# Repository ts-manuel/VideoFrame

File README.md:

# Video Frame

<!-- TABLE OF CONTENTS -->
<details open="open">
  <summary>Table of Contents</summary>
  <ol>
    <li>
      <a href="#about-the-project">About The Project</a>
    </li>
    <li>
      <a href="#getting-started">Getting Started</a>
      <ul>
        <li><a href="#prerequisites">Prerequisites</a></li>
        <li><a href="#compiling">Compiling</a></li>
        <li><a href="#usb-bootloader">USB Bootloader</a></li>
      </ul>
    </li>
    <li><a href="#how-to-operate">How to Operate</a></li>
      <ul>
        <li><a href="#circuit-diagram">Circuit Diagram</a></li>
        <li><a href="#buttons">Buttons</a></li>
        <li><a href="#configuration-through-usb">Configuration through USB</a></li>
      </ul>
    <li><a href="#disclaimer">Disclaimer</a></li>
  </ol>
</details>

<!-- ABOUT THE PROJECT -->
## About The Project
This is a digital picture frame that plays movies at one frame per minute. Images appear on a [7-Color ePaper display](https://www.waveshare.com/5.65inch-e-paper-module-f.htm). The whole movie is stored as a sequence of jpeg images on an SD-Card. An STM32 microcontroller does the jpeg decoding and drives the display.

e-Paper displays maintain the displayed image without needing any power. The image is updated every 24 minutes and an update cycle takes 18 seconds. Since the device is in sleep mode for the majority of the time, power draw is minimal and the batteries last for a decent amount of time.

The device is powered by 6 AA batteries.

For more info check out the [full log on hackaday.io](https://hackaday.io/project/177197-the-slowest-video-player-with-7-colors)

<!-- GETTING STARTED -->
## Getting Started
### Prerequisites
* [STM32CubeIDE 1.4.0](https://www.st.com/en/development-tools/stm32cubeide.html)
* [dfu-util](http://dfu-util.sourceforge.net/)

### Compiling
* Open STM32CubeIDE
* Select a folder as workspace (this can be any folder in your hard-drive)
* Click on `File > Import`
* Select `General > Existing Project into Workspace` then click next
* Browse for the folder `stm32` select the project and click finish

### USB bootloader
* Connect the USB cable, check that the [correct drivers](https://www.hanselman.com/blog/how-to-fix-dfuutil-stm-winusb-zadig-bootloaders-and-other-firmware-flashing-issues-on-windows) are installed
* Enter DFU mode by pressing the RESET while holding down the BOOT button
* Use the following command to flash the firmware

      dfu-util -a0 -s 0x08000000 0 -D "Video Frame.bin"

<!-- HOW TO OPERATE -->
## How to Operate
### Circuit Diagram

### Buttons
* **RESET**: Press during sleep to wake the microcontroller and initiate a display update cycle.
* **BOOT**: Hold down during reset to enter DFU mode. Press during display update to receive commands from the serial port.

### Configuration through USB
The USB emulates a serial port that can be used to configure the device. During normal operation, a timer interrupt wakes the microcontroller every 24 minutes to update the display. An update cycle can also be triggered by pressing the **RESET** button. By default, the microcontroller goes back into sleep mode immediately after the display has been updated. By pressing the **BOOT** button while the display is updating, the microcontroller starts listening for commands on the serial port. After 60 seconds of inactivity, the microcontroller goes back to sleep.

The following is a list of commands that can be entered.
> ***load FOLDER/FILE.jpg*** loads the specified file from the SD card

> ***update*** triggers an update cycle

> ***sleep*** enters sleep mode immediately

<!-- DISCLAIMER -->
## Disclaimer
The following project is shared "as is", with the sole objective of being useful. The creator of the described piece of hardware and its associated software cannot guarantee its correct functioning under any circumstance. The author of this project will not be held responsible for any material, personal or economic losses to you or any third parties that may arise from using this design. This project will not be used under any circumstances on systems whose responsibility is critical, or from which people's lives depend upon, directly or indirectly.

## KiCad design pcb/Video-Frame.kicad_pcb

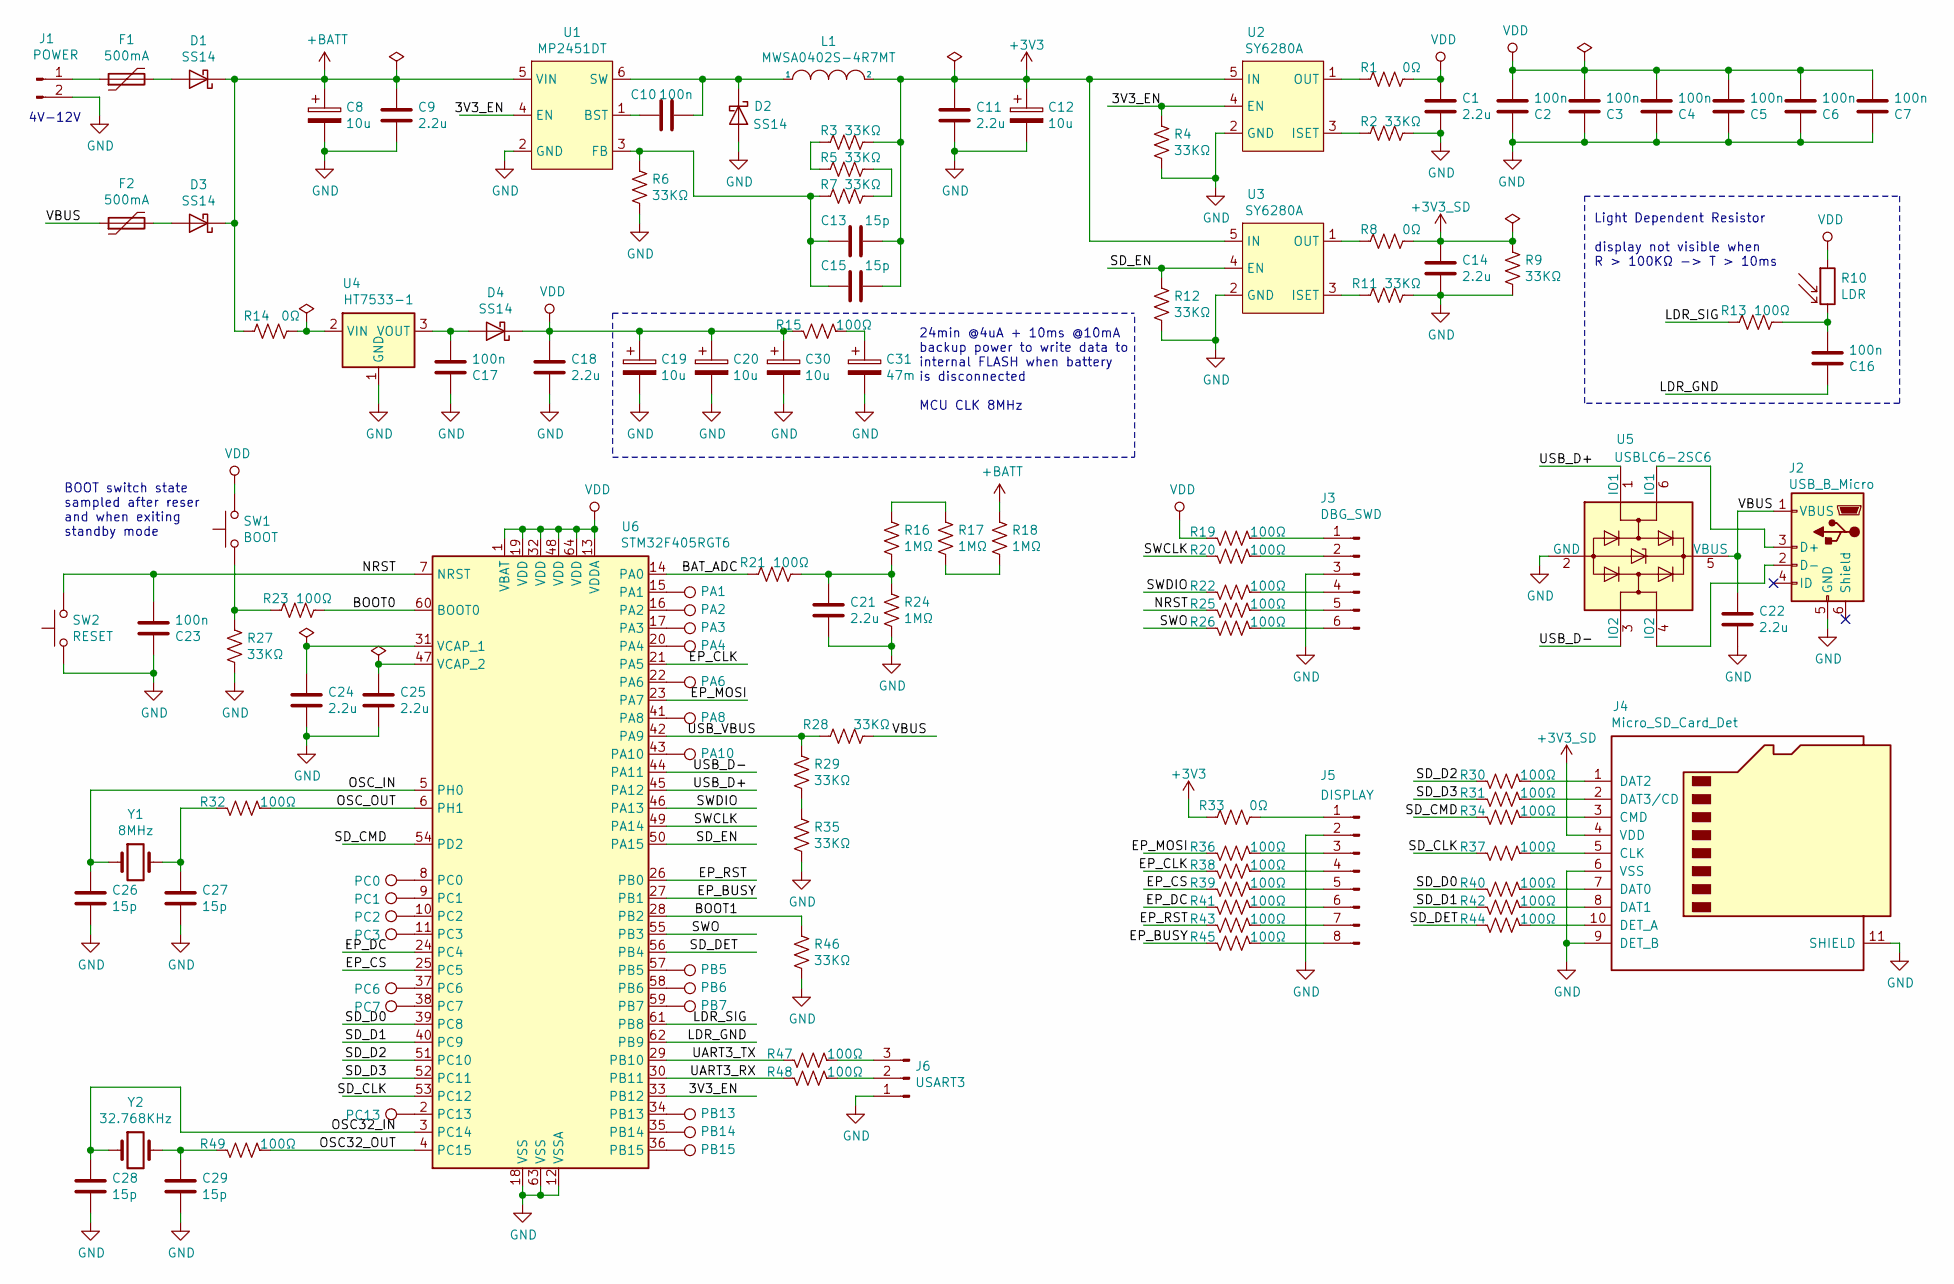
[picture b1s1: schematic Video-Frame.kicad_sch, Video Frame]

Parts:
C1, C9, C11, C14, C18, C21, C22, C24, C25: 2.2u; C_0603_1608Metric; LCSC Footprint 0603
C2, C3, C4, C5, C6, C7, C10, C16, C17, C23: 100n; C_0603_1608Metric; LCSC Footprint 0603
C8, C12, C19, C20, C30: 10u; CP_EIA-3216-10_Kemet-I; LCSC Footprint CASE-A_3216
C13, C15, C26, C27, C28, C29: 15p; C_0603_1608Metric; LCSC Footprint 0603
C31: 47m; CP_Elec_10x7.7; LCSC FC0H473ZFTBR24
D1, D2, D3, D4: SS14; D_SMA; LCSC Footprint SMA,DO-214AC
F1, F2: 500mA; Fuse_1812_4532Metric; LCSC C269127
J1: POWER; PinHeader_1x02_P2.54mm_Vertical
J2: USB_B_Micro; USB_Micro-B_CUI_Devices-UJ2-MIBH-G-SMT-TR
J3: DBG_SWD; PinHeader_1x06_P2.54mm_Vertical
J4: Micro_SD_Card_Det; microSD_HC_Molex_104031-0811
J5: DISPLAY; PinHeader_1x08_P2.54mm_Horizontal
J6: USART3; PinHeader_1x03_P2.54mm_Vertical
L1: MWSA0402S-4R7MT; L_Murata_LQH55DN_5.7x5.0mm; LCSC Footprint SMD-4.2x4.4x2.0
R1, R8, R14, R33: 0Ω; R_0603_1608Metric; LCSC Footprint 0603
R2, R3, R4, R5, R6, R7, R9, R11, R12, R27, R28, R29, R35, R46: 33KΩ; R_0603_1608Metric; LCSC Footprint 0603
R10: LDR; R_LDR_5.1x4.3mm_P3.4mm_Vertical
R13, R15, R19, R20, R21, R22, R23, R25, R26, R30, R31, R32, R34, R36, R37, R38, R39, R40, R41, R42, R43, R44, R45, R47, R48, R49: 100Ω; R_0603_1608Metric; LCSC Footprint 0603
R16, R17, R18, R24: 1MΩ; R_0603_1608Metric; LCSC Footprint 0603
SW1: BOOT; SW_PUSH_6mm
SW2: RESET; SW_PUSH_6mm
TP1: PA1; TestPoint_Pad_D1.0mm
TP2: PA2; TestPoint_Pad_D1.0mm
TP3: PA3; TestPoint_Pad_D1.0mm
TP4: PA4; TestPoint_Pad_D1.0mm
TP5: PA6; TestPoint_Pad_D1.0mm
TP6: PA8; TestPoint_Pad_D1.0mm
TP7: PA10; TestPoint_Pad_D1.0mm
TP8: PC0; TestPoint_Pad_D1.0mm
TP9: PC1; TestPoint_Pad_D1.0mm
TP10: PC2; TestPoint_Pad_D1.0mm
TP11: PC3; TestPoint_Pad_D1.0mm
TP12: PB5; TestPoint_Pad_D1.0mm
TP13: PC6; TestPoint_Pad_D1.0mm
TP14: PB6; TestPoint_Pad_D1.0mm
TP15: PC7; TestPoint_Pad_D1.0mm
TP16: PB7; TestPoint_Pad_D1.0mm
TP17: PC13; TestPoint_Pad_D1.0mm
TP18: PB13; TestPoint_Pad_D1.0mm
TP19: PB14; TestPoint_Pad_D1.0mm
TP20: PB15; TestPoint_Pad_D1.0mm
U1: MP2451DT; SOT-23-6_Handsoldering; LCSC Footprint SOT-23-6L
U2, U3: SY6280A; SOT-23-5_HandSoldering; LCSC Footprint SOT-23-5
U4: HT7533-1; SOT-89-3; LCSC Footprint SOT-89-3
U5: USBLC6-2SC6; SOT-23-6; LCSC Footprint SOT-23-6L
U6: STM32F405RGT6; LQFP-64_10x10mm_P0.5mm; LCSC Footprint LQFP-64_10.0x10.0x0.5P
Y1: 8MHz; Crystal_SMD_5032-2Pin_5.0x3.2mm; LCSC Footprint SMD-5032_2P
Y2: 32.768KHz; Crystal_SMD_3215-2Pin_3.2x1.5mm; LCSC Footprint SMD-3215_2P

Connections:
+3V3: C11.1, C12.1, C13.2, C15.2, L1.2, R3.2, R33.1, U2.5 (IN), U3.5 (IN)
+3V3_SD: C14.1, J4.4 (VDD), R8.2, R9.1
+BATT: C8.1, C9.1, D1.1 (K), D3.1 (K), R14.2, R18.1, U1.5 (VIN)
/3V3_EN: R4.1, U1.4 (EN), U2.4 (EN), U6.33 (PB12)
/BAT_ADC: R21.1, U6.14 (PA0)
/BOOT0: R23.2, U6.60 (BOOT0)
/BOOT1: R46.1, U6.28 (PB2)
/EP_BUSY: R45.1, U6.27 (PB1)
/EP_CLK: R38.1, U6.21 (PA5)
/EP_CS: R39.1, U6.25 (PC5)
/EP_DC: R41.1, U6.24 (PC4)
/EP_MOSI: R36.1, U6.23 (PA7)
/EP_RST: R43.1, U6.26 (PB0)
/LDR_GND: C16.1, U6.62 (PB9)
/LDR_SIG: R13.1, U6.61 (PB8)
/NRST: C23.2, R25.1, SW2.2, U6.7 (NRST)
/OSC32_IN: C28.1, U6.3 (PC14), Y2.1
/OSC32_OUT: R49.2, U6.4 (PC15)
/OSC_IN: C26.1, U6.5 (PH0), Y1.1
/OSC_OUT: R32.2, U6.6 (PH1)
/SD_CLK: R37.1, U6.53 (PC12)
/SD_CMD: R34.1, U6.54 (PD2)
/SD_D0: R40.1, U6.39 (PC8)
/SD_D1: R42.1, U6.40 (PC9)
/SD_D2: R30.1, U6.51 (PC10)
/SD_D3: R31.1, U6.52 (PC11)
/SD_DET: R44.1, U6.56 (PB4)
/SD_EN: R12.1, U3.4 (EN), U6.50 (PA15)
/SWCLK: R20.1, U6.49 (PA14)
/SWDIO: R22.1, U6.46 (PA13)
/SWO: R26.1, U6.55 (PB3)
/UART3_RX: R48.1, U6.30 (PB11)
/UART3_TX: R47.1, U6.29 (PB10)
/USB_D+: U5.1 (IO1), U6.45 (PA12)
/USB_D-: U5.3 (IO2), U6.44 (PA11)
/USB_VBUS: R28.1, R29.1, U6.42 (PA9)
/VBUS: C22.1, F2.1, J2.1 (VBUS), R28.2, U5.5 (VBUS)
GND: C1.2, C2.1, C3.1, C4.1, C5.1, C6.1, C7.1, C8.2, C9.2, C11.2, C12.2, C14.2, C17.1, C18.2, C19.2, C20.2, C21.2, C22.2, C23.1, C24.2, C25.2, C26.2, C27.2, C28.2, C29.2, C30.2, C31.2, D2.2 (A), J1.2, J2.5 (GND), J3.3, J4.6 (VSS), J4.9 (DET_B), J4.11 (SHIELD), J5.2, J6.1, R2.2, R4.2, R6.2, R9.2, R11.2, R12.2, R24.2, R27.2, R35.2, R46.2, SW2.1, U1.2 (GND), U2.2 (GND), U3.2 (GND), U4.1 (GND), U5.2 (GND), U6.12 (VSSA), U6.18 (VSS), U6.63 (VSS)
unnamed: C10.1, D2.1 (K), L1.1, U1.6 (SW)
unnamed: C10.2, U1.1 (BST)
unnamed: C13.1, C15.1, R6.1, R7.1, U1.3 (FB)
unnamed: C16.2, R10.2, R13.2
unnamed: C17.2, D4.2 (A), U4.3 (VOUT)
unnamed: C21.1, R16.2, R21.2, R24.1
unnamed: C24.1, U6.31 (VCAP_1)
unnamed: C25.1, U6.47 (VCAP_2)
unnamed: C27.1, R32.1, Y1.2
unnamed: C29.1, R49.1, Y2.2
unnamed: C31.1, R15.2
unnamed: D1.2 (A), F1.2
unnamed: D3.2 (A), F2.2
unnamed: F1.1, J1.1
unnamed: J2.2 (D-), U5.4 (IO2)
unnamed: J2.3 (D+), U5.6 (IO1)
unnamed: J3.1, R19.2
unnamed: J3.2, R20.2
unnamed: J3.4, R22.2
unnamed: J3.5, R25.2
unnamed: J3.6, R26.2
unnamed: J4.1 (DAT2), R30.2
unnamed: J4.2 (DAT3/CD), R31.2
unnamed: J4.3 (CMD), R34.2
unnamed: J4.5 (CLK), R37.2
unnamed: J4.7 (DAT0), R40.2
unnamed: J4.8 (DAT1), R42.2
unnamed: J4.10 (DET_A), R44.2
unnamed: J5.1, R33.2
unnamed: J5.3, R36.2
unnamed: J5.4, R38.2
unnamed: J5.5, R39.2
unnamed: J5.6, R41.2
unnamed: J5.7, R43.2
unnamed: J5.8, R45.2
unnamed: J6.2, R48.2
unnamed: J6.3, R47.2
unnamed: R1.1, U2.1 (OUT)
unnamed: R2.1, U2.3 (ISET)
unnamed: R3.1, R5.1
unnamed: R5.2, R7.2
unnamed: R8.1, U3.1 (OUT)
unnamed: R11.1, U3.3 (ISET)
unnamed: R16.1, R17.1
unnamed: R17.2, R18.2
unnamed: R23.1, R27.1, SW1.1
unnamed: R29.2, R35.1
unnamed: TP1.1, U6.15 (PA1)
unnamed: TP2.1, U6.16 (PA2)
unnamed: TP3.1, U6.17 (PA3)
unnamed: TP4.1, U6.20 (PA4)
unnamed: TP5.1, U6.22 (PA6)
unnamed: TP6.1, U6.41 (PA8)
unnamed: TP7.1, U6.43 (PA10)
unnamed: TP8.1, U6.8 (PC0)
unnamed: TP9.1, U6.9 (PC1)
unnamed: TP10.1, U6.10 (PC2)
unnamed: TP11.1, U6.11 (PC3)
unnamed: TP12.1, U6.57 (PB5)
unnamed: TP13.1, U6.37 (PC6)
unnamed: TP14.1, U6.58 (PB6)
unnamed: TP15.1, U6.38 (PC7)
unnamed: TP16.1, U6.59 (PB7)
unnamed: TP17.1, U6.2 (PC13)
unnamed: TP18.1, U6.34 (PB13)
unnamed: TP19.1, U6.35 (PB14)
unnamed: TP20.1, U6.36 (PB15)
unnamed: R14.1, U4.2 (VIN)
VDD: C1.1, C2.2, C3.2, C4.2, C5.2, C6.2, C7.2, C18.1, C19.1, C20.1, C30.1, D4.1 (K), R1.2, R10.1, R15.1, R19.1, SW1.2, U6.1 (VBAT), U6.13 (VDDA), U6.19 (VDD), U6.32 (VDD), U6.48 (VDD), U6.64 (VDD)

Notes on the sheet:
BOOT switch state sampled after reser and when exiting standby mode
4V-12V
24min @4uA + 10ms @10mA backup power to write data to internal FLASH when battery is disconnected MCU CLK 8MHz
Light Dependent Resistor display not visible when R > 100KΩ -> T > 10ms

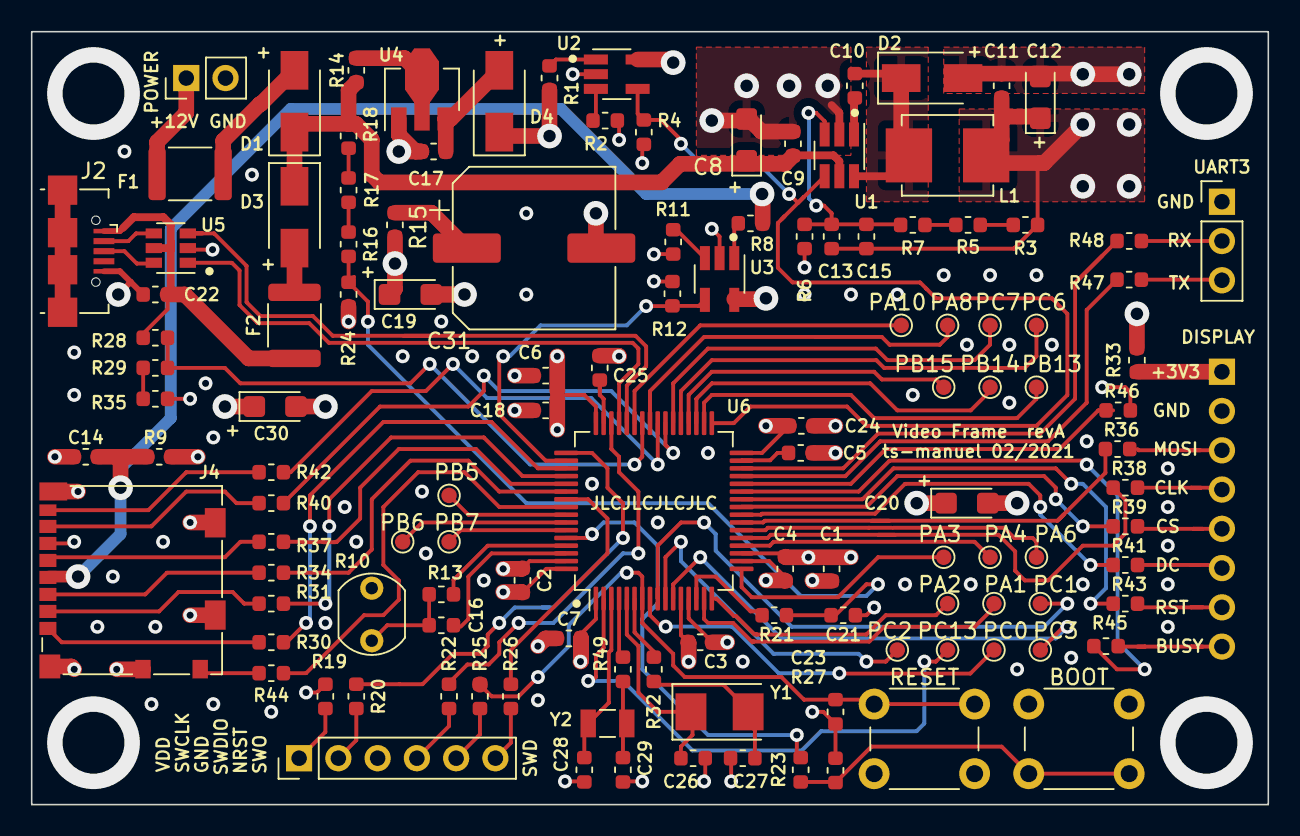
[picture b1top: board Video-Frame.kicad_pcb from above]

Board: 4 copper layers, 80.0 x 50.0 mm, 123 parts (1 on the bottom side), 107 nets.

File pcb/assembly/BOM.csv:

Comment,Designator,Footprint,LCSC
"2.2u","C1,C9,C11,C14,C18,C21,C22,C24,C25","Capacitor_SMD:C_0603_1608Metric","C23630"
"15p","C13,C15,C26,C27,C28,C29","Capacitor_SMD:C_0603_1608Metric","C1644"
"100n","C2,C3,C4,C5,C6,C7,C10,C16,C17,C23","Capacitor_SMD:C_0603_1608Metric","C14663"
"47m","C31","Capacitor_SMD:CP_Elec_10x7.7","FC0H473ZFTBR24"
"10u","C8,C12,C19,C20,C30","Capacitor_Tantalum_SMD:CP_EIA-3216-10_Kemet-I","C7171"
"SS14","D1,D2,D3,D4","Diode_SMD:D_SMA","C2480"
"500mA","F1,F2","Fuse:Fuse_1812_4532Metric","C269127"
"POWER","J1","Connector_PinHeader_2.54mm:PinHeader_1x02_P2.54mm_Vertical","-"
"USB_B_Micro","J2","Connector_MicroUSB:USB_Micro-B_CUI_Devices-UJ2-MIBH-G-SMT-TR","-"
"DBG_SWD","J3","Connector_PinHeader_2.54mm:PinHeader_1x06_P2.54mm_Vertical","-"
"Micro_SD_Card_Det","J4","Connector_Card:microSD_HC_Molex_104031-0811","-"
"DISPLAY","J5","Connector_PinHeader_2.54mm:PinHeader_1x08_P2.54mm_Horizontal","-"
"USART3","J6","Connector_PinHeader_2.54mm:PinHeader_1x03_P2.54mm_Vertical","-"
"MWSA0402S-4R7MT","L1","Inductor_SMD:L_Murata_LQH55DN_5.7x5.0mm","C408337"
"0Ω","R1,R8,R14,R33","Resistor_SMD:R_0603_1608Metric","C21189"
"LDR","R10","OptoDevice:R_LDR_5.1x4.3mm_P3.4mm_Vertical","-"
"100Ω","R13,R15,R19,R20,R21,R22,R23,R25,R26,R30,R31,R32,R34,R36,R37,R38,R39,R40,R41,R42,R43,R44,R45,R47,R48,R49","Resistor_SMD:R_0603_1608Metric","C7250"
"1MΩ","R16,R17,R18,R24","Resistor_SMD:R_0603_1608Metric","C22935"
"33KΩ","R2,R3,R4,R5,R6,R7,R9,R11,R12,R27,R28,R29,R35,R46","Resistor_SMD:R_0603_1608Metric","C4216"
"BOOT","SW1","Button_Switch_THT:SW_PUSH_6mm","-"
"RESET","SW2","Button_Switch_THT:SW_PUSH_6mm","-"
"PA1","TP1","TestPoint:TestPoint_Pad_D1.0mm","-"
"PC2","TP10","TestPoint:TestPoint_Pad_D1.0mm","-"
"PC3","TP11","TestPoint:TestPoint_Pad_D1.0mm","-"
"PB5","TP12","TestPoint:TestPoint_Pad_D1.0mm","-"
"PC6","TP13","TestPoint:TestPoint_Pad_D1.0mm","-"
"PB6","TP14","TestPoint:TestPoint_Pad_D1.0mm","-"
"PC7","TP15","TestPoint:TestPoint_Pad_D1.0mm","-"
"PB7","TP16","TestPoint:TestPoint_Pad_D1.0mm","-"
"PC13","TP17","TestPoint:TestPoint_Pad_D1.0mm","-"
"PB13","TP18","TestPoint:TestPoint_Pad_D1.0mm","-"
"PB14","TP19","TestPoint:TestPoint_Pad_D1.0mm","-"
"PA2","TP2","TestPoint:TestPoint_Pad_D1.0mm","-"
"PB15","TP20","TestPoint:TestPoint_Pad_D1.0mm","-"
"PA3","TP3","TestPoint:TestPoint_Pad_D1.0mm","-"
"PA4","TP4","TestPoint:TestPoint_Pad_D1.0mm","-"
"PA6","TP5","TestPoint:TestPoint_Pad_D1.0mm","-"
"PA8","TP6","TestPoint:TestPoint_Pad_D1.0mm","-"
"PA10","TP7","TestPoint:TestPoint_Pad_D1.0mm","-"
"PC0","TP8","TestPoint:TestPoint_Pad_D1.0mm","-"
"PC1","TP9","TestPoint:TestPoint_Pad_D1.0mm","-"
"MP2451DT","U1","Package_TO_SOT_SMD:SOT-23-6_Handsoldering","C14123"
"SY6280A","U2,U3","Package_TO_SOT_SMD:SOT-23-5_HandSoldering","C207620"
"HT7533-1","U4","Package_TO_SOT_SMD:SOT-89-3","C14289"
"USBLC6-2SC6","U5","Package_TO_SOT_SMD:SOT-23-6","C7519"
"STM32F405RGT6","U6","Package_QFP:LQFP-64_10x10mm_P0.5mm","C15742"
"8MHz","Y1","Crystal:Crystal_SMD_5032-2Pin_5.0x3.2mm","C115962"
"32.768KHz","Y2","Crystal:Crystal_SMD_3215-2Pin_3.2x1.5mm","C32346"

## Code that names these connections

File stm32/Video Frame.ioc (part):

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PH0-OSC_IN.Signal=RCC_OSC_IN
PC10.GPIO_PuPd=GPIO_PULLUP
Mcu.UserName=STM32F405RGTx
PB10.Mode=Asynchronous
PC10.Signal=SDIO_D2
PC12.Signal=SDIO_CK
PC0.GPIOParameters=GPIO_Label
PC0.GPIO_Label=BTN_SLEEP
PA11.Mode=Device_Only
PB0.GPIO_Label=EP_RST
PD2.GPIOParameters=GPIO_PuPd,GPIO_Speed_High_Default,GPIO_Label
PB11.Signal=USART3_RX
RCC.SYSCLKSource=RCC_SYSCLKSOURCE_PLLCLK
PA15.GPIO_Label=PWR_SD_EN
PC11.GPIO_PuPd=GPIO_PULLUP
PB4.GPIOParameters=GPIO_PuPd,GPIO_Label
PA12.Signal=USB_OTG_FS_DP
PC10.GPIO_Speed_High_Default=GPIO_SPEED_FREQ_MEDIUM
PA10.PinState=GPIO_PIN_RESET
PC9.GPIO_Speed_High_Default=GPIO_SPEED_FREQ_MEDIUM
PH0-OSC_IN.Mode=HSE-External-Oscillator
PA0-WKUP.GPIOParameters=GPIO_Label
RCC.HSE_VALUE=8000000
PB3.Mode=Trace_Asynchronous_SW
PB12.GPIO_Label=PWR_3V3_EN
PB0.GPIOParameters=GPIO_Label
PC14-OSC32_IN.Mode=LSE-External-Oscillator
PC4.GPIO_Label=EP_DC
PA14.Mode=Trace_Asynchronous_SW
PB1.GPIO_Label=EP_BUSY
PC11.GPIO_Label=SD_D3
PA10.GPIO_Label=LED0
PC9.Mode=SD_4_bits_Wide_bus
PH1-OSC_OUT.Mode=HSE-External-Oscillator
PC8.GPIOParameters=GPIO_PuPd,GPIO_Speed_High_Default,GPIO_Label
Mcu.Package=LQFP64
PB9.Signal=GPIO_Output
PB1.Signal=GPIO_Input
PA10.Signal=GPIO_Output
PA15.Signal=GPIO_Output
PA5.GPIOParameters=GPIO_Speed
PB8.GPIO_ModeDefaultOutputPP=GPIO_MODE_OUTPUT_OD
PC11.Mode=SD_4_bits_Wide_bus
PC5.Signal=GPIO_Output
PC12.GPIO_PuPd=GPIO_NOPULL
PC4.GPIOParameters=GPIO_Label
PB4.Signal=GPIO_Input
PA5.Mode=Simplex_Bidirectional_Master
PC15-OSC32_OUT.Mode=LSE-External-Oscillator
PB8.GPIOParameters=GPIO_Label,GPIO_ModeDefaultOutputPP
PA7.Mode=Simplex_Bidirectional_Master
PB9.GPIO_Label=LDR_GND
PA15.GPIOParameters=GPIO_Label
PC10.GPIO_Label=SD_D2
PC9.GPIO_Label=SD_D1
PD2.GPIO_PuPd=GPIO_PULLUP
PC11.Signal=SDIO_D3
PC8.Signal=SDIO_D0
PC4.Signal=GPIO_Output
PC10.Mode=SD_4_bits_Wide_bus
PC0.Signal=GPXTI0
PC14-OSC32_IN.Signal=RCC_OSC32_IN
PC11.GPIOParameters=GPIO_PuPd,GPIO_Speed_High_Default,GPIO_Label
PA0-WKUP.GPIO_Label=BAT_ADC
PA0-WKUP.Signal=ADCx_IN0
PB9.GPIOParameters=GPIO_Label
PC8.GPIO_Label=SD_D0
PC12.GPIOParameters=GPIO_PuPd,GPIO_Speed_High_Default,GPIO_Label
PA13.Signal=SYS_JTMS-SWDIO
PB8.GPIO_Label=LDR_SIG
PA9.Mode=Activate_VBUS
PB11.Mode=Asynchronous
PC5.GPIOParameters=GPIO_Label
PA9.Signal=USB_OTG_FS_VBUS
PC11.GPIO_Speed_High_Default=GPIO_SPEED_FREQ_MEDIUM
PB4.GPIO_PuPd=GPIO_PULLUP
PC15-OSC32_OUT.Signal=RCC_OSC32_OUT
PB10.Signal=USART3_TX
PD2.Mode=SD_4_bits_Wide_bus
PA5.Signal=SPI1_SCK
PC12.Mode=SD_4_bits_Wide_bus
board=custom
PA7.GPIO_Speed=GPIO_SPEED_FREQ_LOW
PB4.GPIO_Label=SD_DET
PA10.GPIOParameters=PinState,GPIO_Label
PC9.GPIO_PuPd=GPIO_PULLUP
PH1-OSC_OUT.Signal=RCC_OSC_OUT
PC10.GPIOParameters=GPIO_PuPd,GPIO_Speed_High_Default,GPIO_Label
PA13.Mode=Trace_Asynchronous_SW
PC9.GPIOParameters=GPIO_PuPd,GPIO_Speed_High_Default,GPIO_Label
Mcu.Name=STM32F405RGTx
PC8.Mode=SD_4_bits_Wide_bus
PC12.GPIO_Speed_High_Default=GPIO_SPEED_FREQ_MEDIUM
PC8.GPIO_Speed_High_Default=GPIO_SPEED_FREQ_MEDIUM
PC8.GPIO_PuPd=GPIO_PULLUP
PB3.Signal=SYS_JTDO-SWO
RCC.SYSCLKFreq_VALUE=72000000
PA12.Mode=Device_Only
PC5.GPIO_Label=EP_CS
PC12.GPIO_Label=SD_CLK
PA11.Signal=USB_OTG_FS_DM
PA14.Signal=SYS_JTCK-SWCLK
PA5.GPIO_Speed=GPIO_SPEED_FREQ_LOW
PB8.Signal=GPIO_Output
PC9.Signal=SDIO_D1
PD2.Signal=SDIO_CMD
PD2.GPIO_Speed_High_Default=GPIO_SPEED_FREQ_MEDIUM
PB0.Signal=GPIO_Output
PA7.GPIOParameters=GPIO_Speed
PB12.GPIOParameters=GPIO_Label
PB12.Signal=GPIO_Output
PD2.GPIO_Label=SD_CMD
PB1.GPIOParameters=GPIO_Label
PA7.Signal=SPI1_MOSI

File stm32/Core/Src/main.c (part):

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  __HAL_RCC_GPIOD_CLK_ENABLE();

  /*Configure GPIO pin Output Level */
  HAL_GPIO_WritePin(GPIOC, EP_DC_Pin|EP_CS_Pin, GPIO_PIN_RESET);

  /*Configure GPIO pin Output Level */
  HAL_GPIO_WritePin(GPIOB, EP_RST_Pin|PWR_3V3_EN_Pin|LDR_SIG_Pin|LDR_GND_Pin, GPIO_PIN_RESET);

  /*Configure GPIO pin Output Level */
  HAL_GPIO_WritePin(GPIOA, LED0_Pin|PWR_SD_EN_Pin, GPIO_PIN_RESET);

  /*Configure GPIO pins : PC13 PC1 PC2 PC3
                           PC6 PC7 */
  GPIO_InitStruct.Pin = GPIO_PIN_13|GPIO_PIN_1|GPIO_PIN_2|GPIO_PIN_3
                          |GPIO_PIN_6|GPIO_PIN_7;
  GPIO_InitStruct.Mode = GPIO_MODE_ANALOG;
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  GPIO_InitStruct.Pull = GPIO_NOPULL;
  HAL_GPIO_Init(BTN_SLEEP_GPIO_Port, &GPIO_InitStruct);

  /*Configure GPIO pins : BAT_ADC_Pin PA1 PA2 PA3
                           PA4 PA6 PA8 */
  GPIO_InitStruct.Pin = BAT_ADC_Pin|GPIO_PIN_1|GPIO_PIN_2|GPIO_PIN_3
                          |GPIO_PIN_4|GPIO_PIN_6|GPIO_PIN_8;
  GPIO_InitStruct.Mode = GPIO_MODE_ANALOG;
  GPIO_InitStruct.Pull = GPIO_NOPULL;
  HAL_GPIO_Init(GPIOA, &GPIO_InitStruct);

  /*Configure GPIO pins : EP_DC_Pin EP_CS_Pin */
  GPIO_InitStruct.Pin = EP_DC_Pin|EP_CS_Pin;
  GPIO_InitStruct.Mode = GPIO_MODE_OUTPUT_PP;
  GPIO_InitStruct.Pull = GPIO_NOPULL;
  GPIO_InitStruct.Speed = GPIO_SPEED_FREQ_LOW;
  HAL_GPIO_Init(GPIOC, &GPIO_InitStruct);

  /*Configure GPIO pins : EP_RST_Pin PWR_3V3_EN_Pin LDR_GND_Pin */
  GPIO_InitStruct.Pin = EP_RST_Pin|PWR_3V3_EN_Pin|LDR_GND_Pin;
  GPIO_InitStruct.Mode = GPIO_MODE_OUTPUT_PP;
  GPIO_InitStruct.Pull = GPIO_NOPULL;
  GPIO_InitStruct.Speed = GPIO_SPEED_FREQ_LOW;
  HAL_GPIO_Init(GPIOB, &GPIO_InitStruct);

  /*Configure GPIO pin : EP_BUSY_Pin */
  GPIO_InitStruct.Pin = EP_BUSY_Pin;
  GPIO_InitStruct.Mode = GPIO_MODE_INPUT;
  GPIO_InitStruct.Pull = GPIO_NOPULL;
  HAL_GPIO_Init(EP_BUSY_GPIO_Port, &GPIO_InitStruct);

  /*Configure GPIO pins : PB2 PB13 PB14 PB15
                           PB5 PB6 PB7 */
  GPIO_InitStruct.Pin = GPIO_PIN_2|GPIO_PIN_13|GPIO_PIN_14|GPIO_PIN_15
                          |GPIO_PIN_5|GPIO_PIN_6|GPIO_PIN_7;
  GPIO_InitStruct.Mode = GPIO_MODE_ANALOG;
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  GPIO_InitStruct.Speed = GPIO_SPEED_FREQ_LOW;
  HAL_GPIO_Init(GPIOA, &GPIO_InitStruct);

  /*Configure GPIO pin : SD_DET_Pin */
  GPIO_InitStruct.Pin = SD_DET_Pin;
  GPIO_InitStruct.Mode = GPIO_MODE_INPUT;
  GPIO_InitStruct.Pull = GPIO_PULLUP;
  HAL_GPIO_Init(SD_DET_GPIO_Port, &GPIO_InitStruct);

  /*Configure GPIO pin : LDR_SIG_Pin */
  GPIO_InitStruct.Pin = LDR_SIG_Pin;
  GPIO_InitStruct.Mode = GPIO_MODE_OUTPUT_OD;
  GPIO_InitStruct.Pull = GPIO_NOPULL;
  GPIO_InitStruct.Speed = GPIO_SPEED_FREQ_LOW;
  HAL_GPIO_Init(LDR_SIG_GPIO_Port, &GPIO_InitStruct);

  /* EXTI interrupt init*/
  HAL_NVIC_SetPriority(EXTI0_IRQn, 5, 0);
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
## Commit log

2021-01-30 Display test
2021-02-06 Command parser and display test patterns
2021-02-18 JPEG Decoding and Floyd-Steinberg Dithering
2021-02-22 Added Schematic, Changed target MCU to STM32F405RGT6
2021-02-24 PCB Layout
    Changes in schematic
    + Fixed +3V3_SD Power NET
    + Changed 100uF electrolytic to 10uF tantalum (lower leakage current)
2021-02-27 Updated schematic and PCB Layout
    Changes in schematic
    + Added super capacitor on VDD
    + Added notes
2021-02-28 Fixed D2 orientation in CPL file
2021-02-28 RTC wakeup interrupt to update the display
2021-03-01 Added enclosure 3D models
2021-03-02 Fixed Load Command
2021-03-02 Adjustable VCOM Voltage
2021-03-05 Disabled compilation for unused code
2021-03-06 Removed gamma correction
2021-03-06 Added Start and Stop commands, backspace
2021-03-07 Optimize compiler for speed
2021-03-14 Fixed command parser, added color gradients, fixed dithering algorithm
    Command parser:
    + back spaces
    + alarm sound when buffer is full
    Color gradients:
    + color gradients for testing
    Dithering algorithm:
2021-04-04 Code ported to STM32F405RGT
2021-04-05 Fixed 100 Ohm resistors part number
2021-04-05 Added test files
2021-04-10 Added standby mode
    STM32 enters standby mode after display update,
    DC-DC converter and SD powered off during standby,
    SD card communicates with 4bit bus
2021-06-12 FreeRTOS implementation
    Updated STM32CubeIDE to version 1.6.1
    Added battery_task: reads battery voltage every second
2021-06-13 Added console_task
    Implemented start/stop commands and low power mode timeout
2021-06-14 Added display_task
2021-06-14 Added command task-info
    task-info prints information about created tasks (state, stack space, priority)
2021-06-18 SD doesn't work
2021-06-26 Enabled DMA, SD still doesn't work
2021-06-26 Porting to STM32CubeIDE 1.4.0
    Works only in release mode!!!
2021-06-26 Optimized JPEG read from file
2021-06-27 Task definition with CubeMX
2021-06-28 Display update on wakeup interrupt
2021-07-03 Added USB CDC
2021-07-22 Added splash screen when SD can't be read
2021-07-24 Implemented internal FLASH storage
2021-09-04 Updated first file search routine
    File names don't need to start at 0000.jpg any more.
2022-08-14 Added help command
2022-08-14 Added light sensing
    The display now doesn't update if its too dark to see
2022-09-12 Fixed multiple command handling

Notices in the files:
stm32/Core/Src/main.c:
© Copyright (c) 2021 STMicroelectronics.
All rights reserved.
This software component is licensed by ST under BSD 3-Clause license,
the "License"; You may not use this file except in compliance with the
License. You may obtain a copy of the License at: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
(C) COPYRIGHT STMicroelectronics *****END OF FILE
